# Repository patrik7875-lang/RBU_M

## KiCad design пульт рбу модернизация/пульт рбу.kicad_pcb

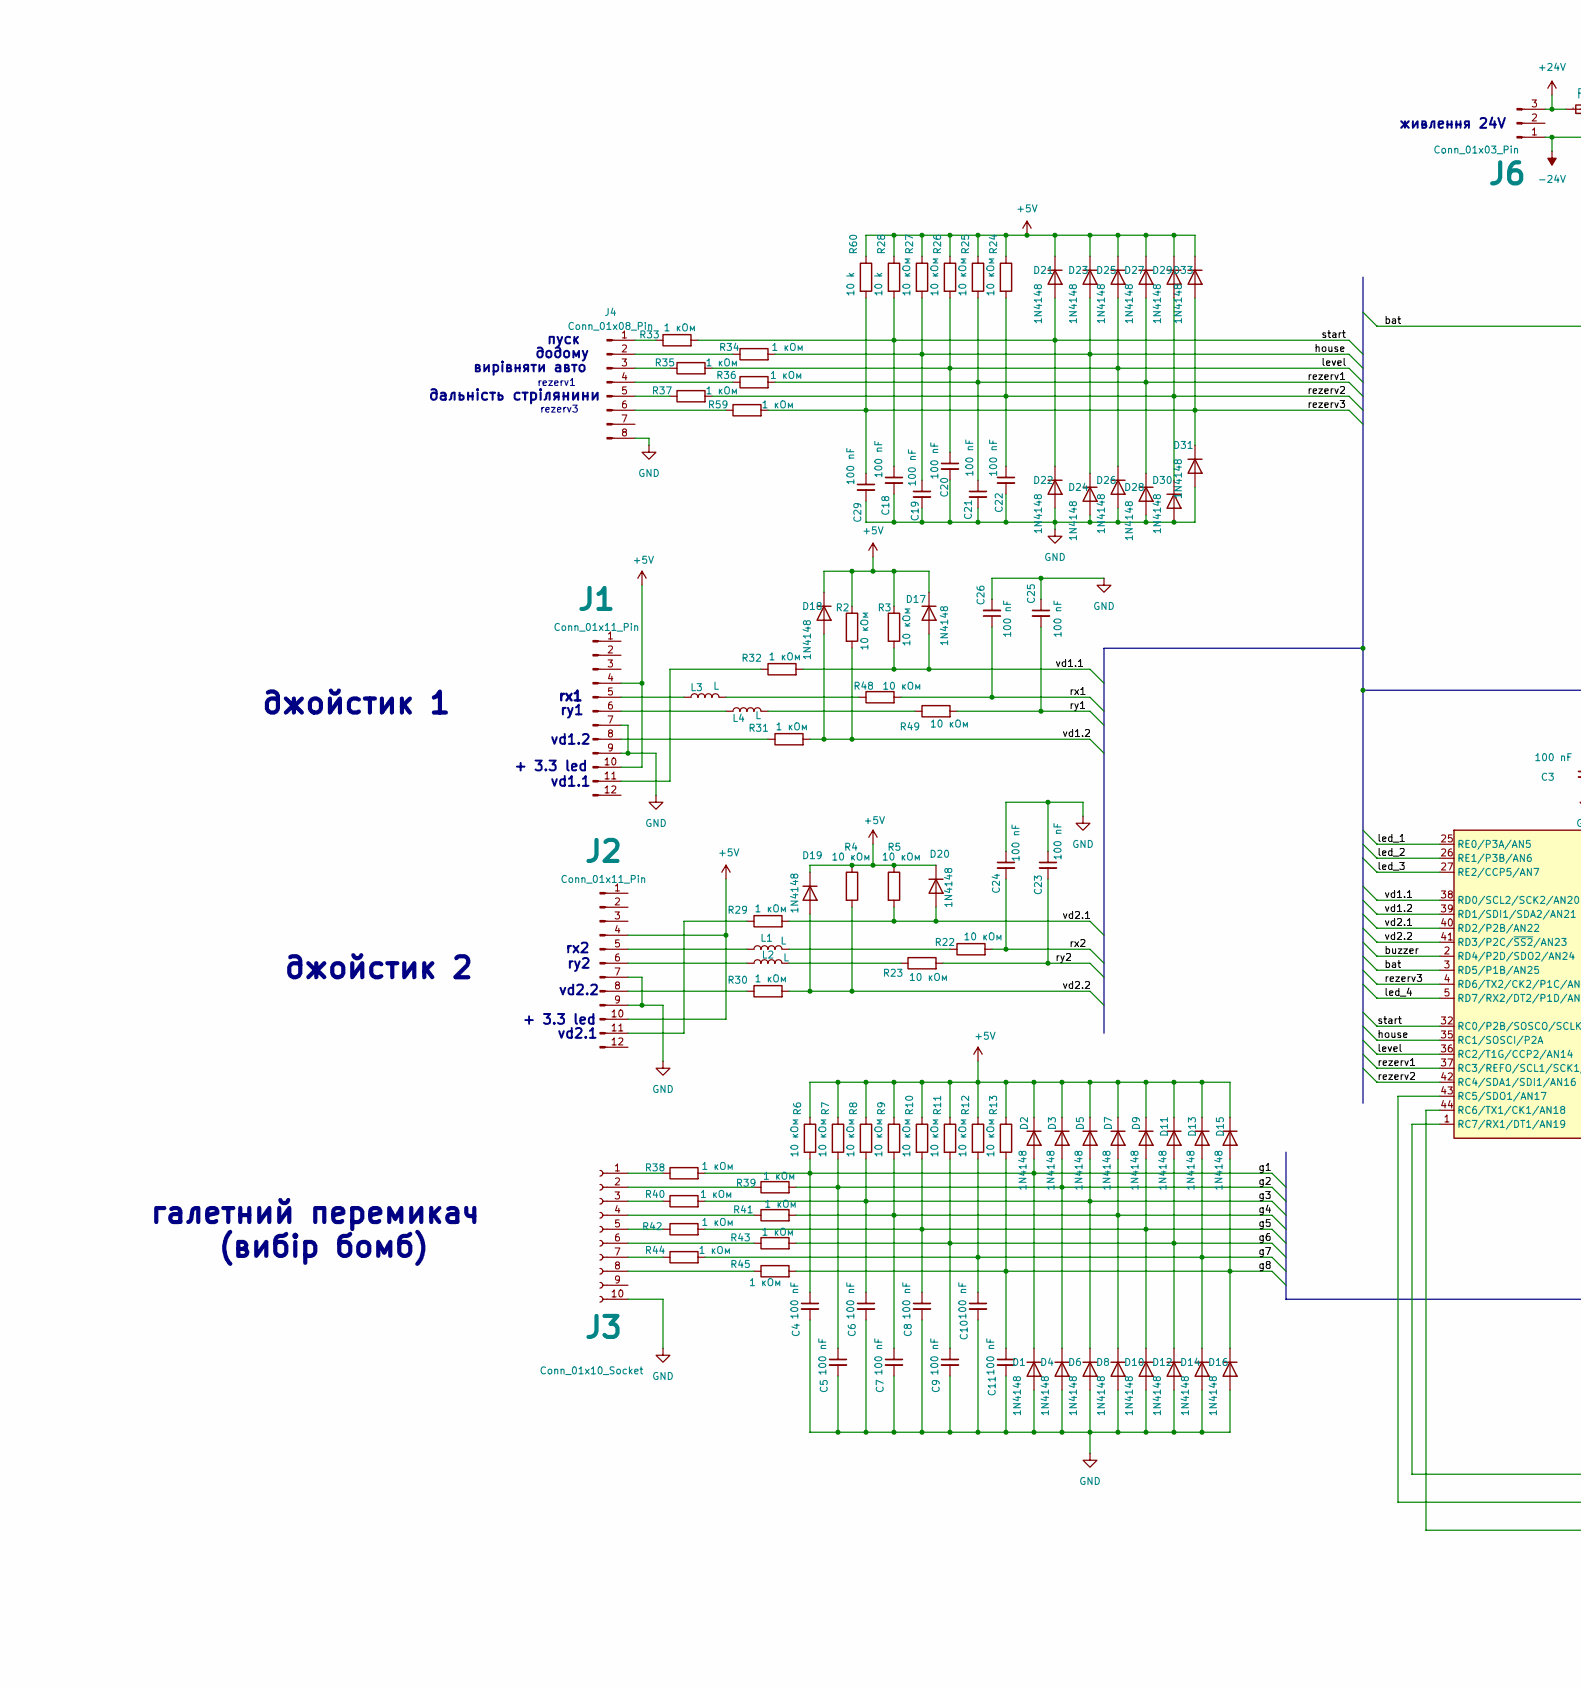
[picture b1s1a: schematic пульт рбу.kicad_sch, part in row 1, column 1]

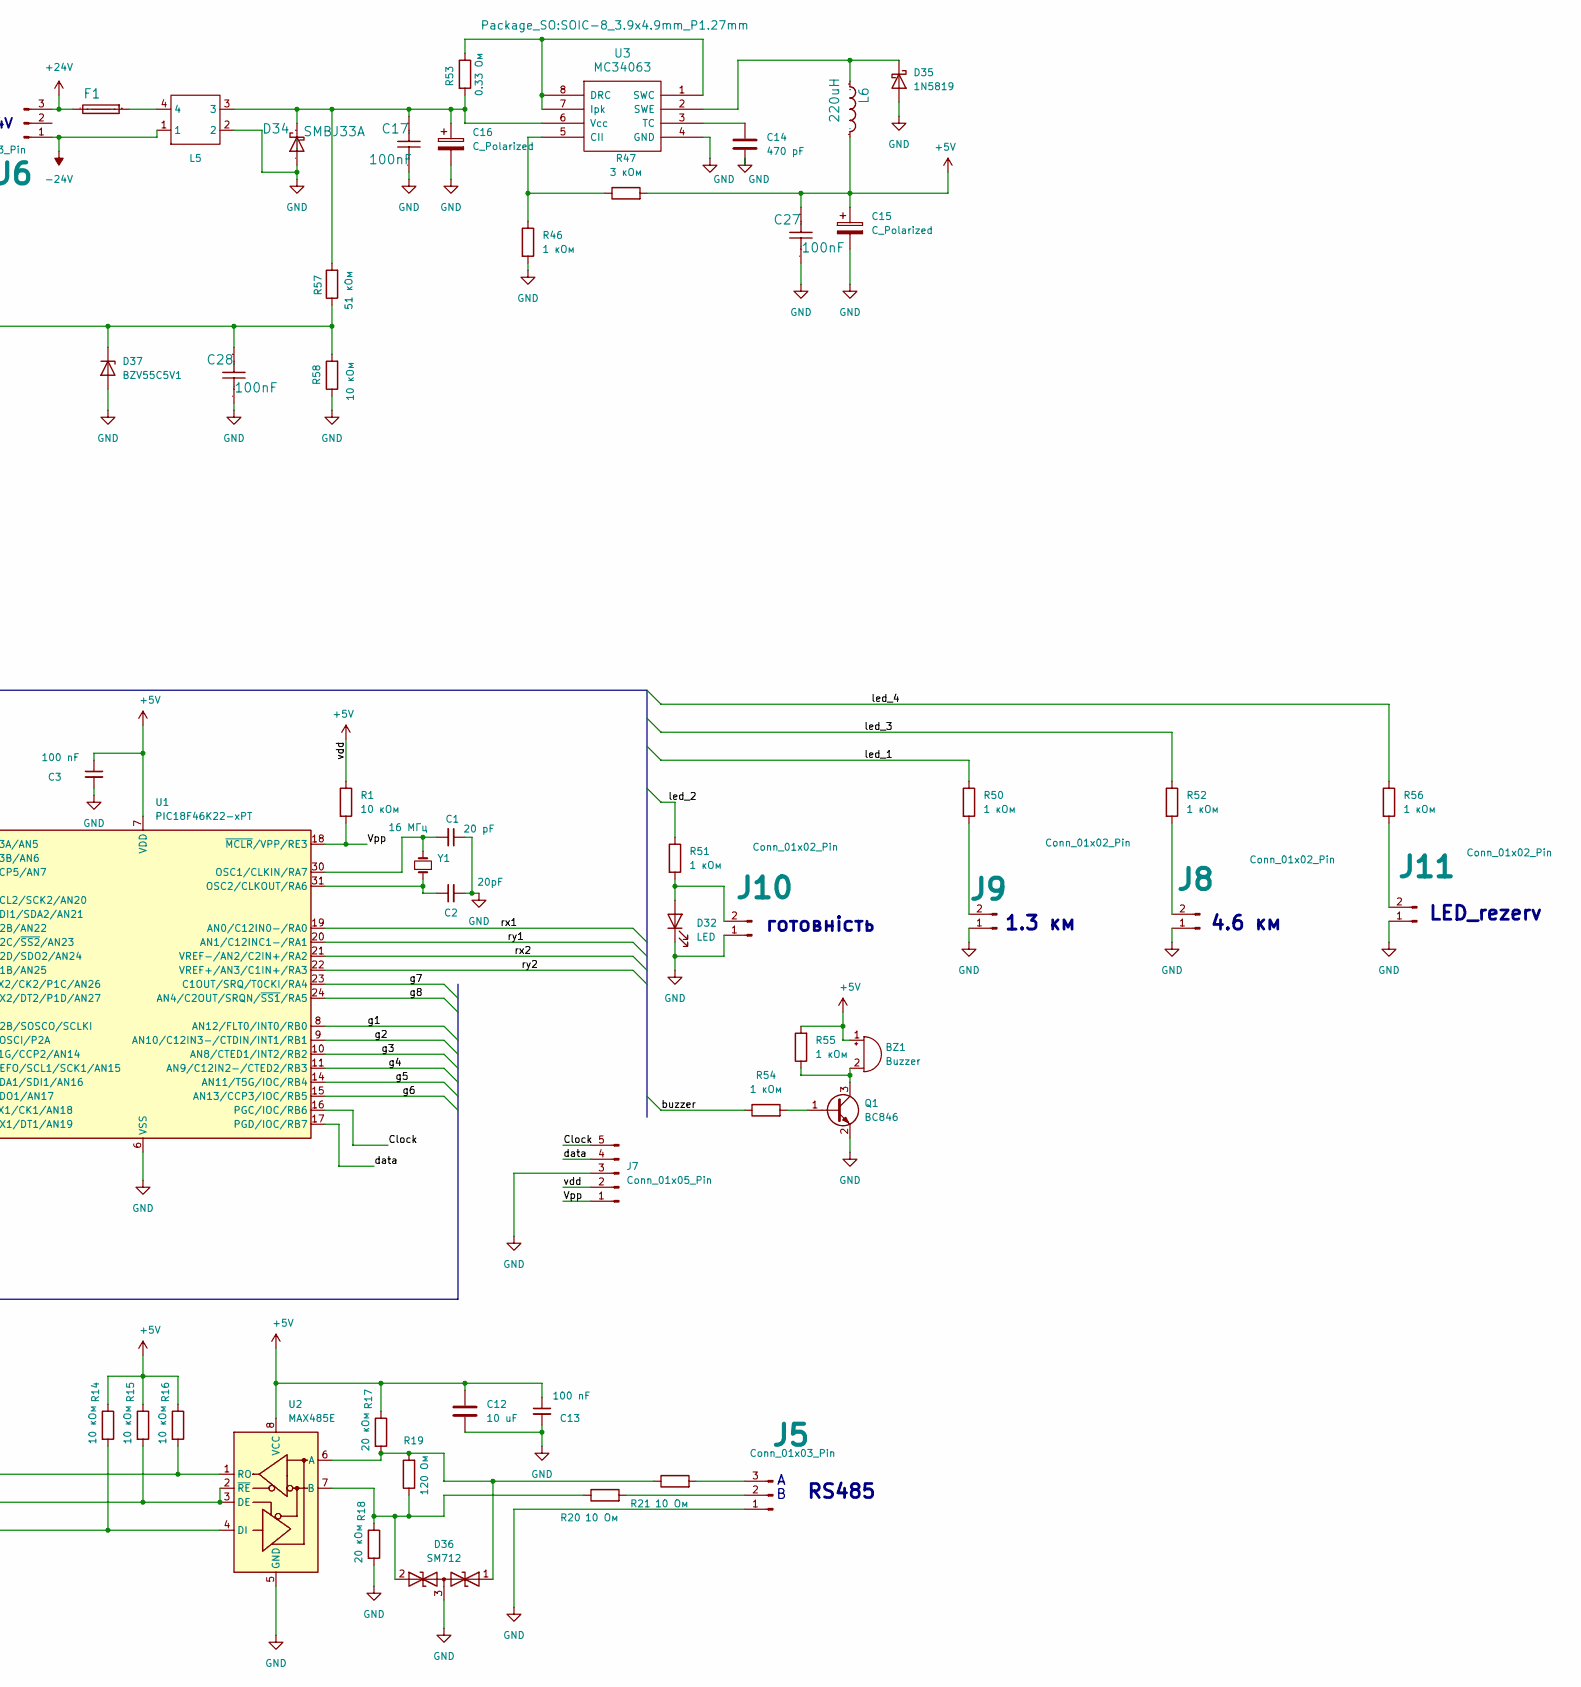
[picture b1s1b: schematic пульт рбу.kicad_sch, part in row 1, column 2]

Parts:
BZ1: Buzzer; Buzzer_12x9.5RM7.6
C1: 20 pF; C_0805_2012Metric
C2: 20pF; C_0805_2012Metric
C3, C4, C5, C6, C7, C8, C9, C10, C11, C13, C18, C19, C20, C21, C22, C23, C24, C25, C26, C29: 100 nF; C_1206_3216Metric
C12: 10 uF; C_1206_3216Metric
C14: 470 pF; C_0805_2012Metric
C15, C16: C_Polarized; C_Radial_D10.0mm_H16.0mm_P5.00mm
C17, C27, C28: 100nF; C_1206_3216Metric; Manufacturer Part FCC0805B104M500DT
D1, D2, D3, D4, D5, D6, D7, D8, D9, D10, D11, D12, D13, D14, D15, D16, D17, D18, D19, D20, D21, D22, D23, D24, D25, D26, D27, D28, D29, D30, D31, D33: 1N4148; D_SOD-123
D32: LED; LED_1206_3216Metric
D34: SMBJ33A; D_SMB
D35: 1N5819; D_DO-41_SOD81_P10.16mm_Horizontal
D36: SM712; SOT-23
D37: BZV55C5V1; D_MiniMELF
F1: 0.5 A; Fuse_1206_3216Metric; Manufacturer Part JFC2410-0200FS
J1, J2: Conn_01x11_Pin; JST_PH_B12B-PH-K_1x12_P2.00mm_Vertical
J3: Conn_01x10_Socket; Molex_KK-254_AE-6410-10A_1x10_P2.54mm_Vertical
J4: Conn_01x08_Pin; Molex_KK-254_AE-6410-08A_1x08_P2.54mm_Vertical
J5, J6: Conn_01x03_Pin; Molex_KK-254_AE-6410-03A_1x03_P2.54mm_Vertical
J7: Conn_01x05_Pin; PinHeader_1x05_P2.54mm_Vertical
J8, J9, J10, J11: Conn_01x02_Pin; JST_PH_B2B-PH-K_1x02_P2.00mm_Vertical
L1, L2, L3, L4: L; L_0805_2012Metric
L5: SSRH7H-M20016
L6: 220uH; L_Changjiang_FXL0840; Manufacturer Part CYL104R-10UH
Q1: BC846; SOT-23
R1, R4, R5: 10 кОм; Fuse_1206_3216Metric
R2, R3, R6, R7, R8, R9, R10, R11, R12, R13, R14, R15, R16, R24, R25, R26, R27: 10 кОм; R_1206_3216Metric
R17, R18: 20 кОм; R_1206_3216Metric
R19: 120 Ом; R_1206_3216Metric
R20, R21: 10 Ом; R_1206_3216Metric
R22, R23, R48, R49, R58: 10 кОм; R_0805_2012Metric
R28, R60: 10 k; R_1206_3216Metric
R29, R30, R31, R32, R33, R34, R35, R36, R37, R38, R39, R40, R41, R42, R43, R44, R45, R46, R50, R51, R52, R54, R55, R56, R59: 1 кОм; R_0805_2012Metric
R47: 3 кОм; R_0805_2012Metric
R53: 0.33 Ом; R_Axial_DIN0207_L6.3mm_D2.5mm_P2.54mm_Vertical
R57: 51 кОм; R_0805_2012Metric
U1: PIC18F46K22-xPT; TQFP-44_10x10mm_P0.8mm
U2: MAX485E; SOIC-8_3.9x4.9mm_P1.27mm
U3: MC34063; SOIC-8_3.9x4.9mm_P1.27mm
Y1: 16 МГц; Crystal_HC18-U_Vertical

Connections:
+5V: BZ1.1 (+), C3.1, C12.1, C13.1, C15.1, C27.1, D2.1 (K), D3.1 (K), D5.1 (K), D7.1 (K), D9.1 (K), D11.1 (K), D13.1 (K), D15.1 (K), D17.1 (K), D18.1 (K), D19.1 (K), D20.1 (K), D21.1 (K), D23.1 (K), D25.1 (K), D27.1 (K), D29.1 (K), D33.1 (K), J1.4, J1.10, J2.4, J2.10, J7.2, L6.2, R1.1, R2.1, R3.1, R4.1, R5.1, R6.1, R7.1, R8.1, R9.1, R10.1, R11.1, R12.1, R13.1, R14.1, R15.1, R16.1, R17.1, R24.1, R25.1, R26.1, R27.1, R28.1, R47.2, R55.2, R60.1, U1.7 (VDD), U1.28 (VDD), U2.8 (VCC)
+24V: F1.2, J6.3
-24V: J6.1, L5.1
/Clock: J7.5, U1.16 (PGC/IOC/RB6)
/Vpp: J7.1, R1.2, U1.18 (~MCLR/VPP/RE3)
/bat: C28.1, D37.1 (K), R57.1, R58.2, U1.3 (RD5/P1B/AN25)
/buzzer: R54.1, U1.2 (RD4/P2D/SDO2/AN24)
/data: J7.4, U1.17 (PGD/IOC/RB7)
/g1: C4.1, D1.1 (K), D2.2 (A), R6.2, R38.2, U1.8 (AN12/FLT0/INT0/RB0)
/g2: C5.1, D3.2 (A), D4.1 (K), R7.2, R39.2, U1.9 (AN10/C12IN3-/CTDIN/INT1/RB1)
/g3: C6.1, D5.2 (A), D6.1 (K), R8.2, R40.2, U1.10 (AN8/CTED1/INT2/RB2)
/g4: C7.1, D7.2 (A), D8.1 (K), R9.2, R41.2, U1.11 (AN9/C12IN2-/CTED2/RB3)
/g5: C8.1, D9.2 (A), D10.1 (K), R10.2, R42.2, U1.14 (AN11/T5G/IOC/RB4)
/g6: C9.1, D11.2 (A), D12.1 (K), R11.2, R43.2, U1.15 (AN13/CCP3/IOC/RB5)
/g7: C10.1, D13.2 (A), D14.1 (K), R12.2, R44.2, U1.23 (C1OUT/SRQ/T0CKI/RA4)
/g8: C11.1, D15.2 (A), D16.1 (K), R13.2, R45.2, U1.24 (AN4/C2OUT/SRQN/~SS1/RA5)
/house: C19.1, D23.2 (A), D24.1 (K), R27.2, R34.2, U1.35 (RC1/SOSCI/P2A)
/led_1: R50.1, U1.25 (RE0/P3A/AN5)
/led_2: R51.1, U1.26 (RE1/P3B/AN6)
/led_3: R52.1, U1.27 (RE2/CCP5/AN7)
/led_4: R56.1, U1.5 (RD7/RX2/DT2/P1D/AN27)
/level: C20.1, D25.2 (A), D26.1 (K), R26.2, R35.2, U1.36 (RC2/T1G/CCP2/AN14)
/rezerv1: C21.1, D27.2 (A), D28.1 (K), R25.2, R36.2, U1.37 (RC3/REFO/SCL1/SCK1/AN15)
/rezerv2: C22.1, D29.2 (A), D30.1 (K), R24.2, R37.2, U1.42 (RC4/SDA1/SDI1/AN16)
/rezerv3: C29.1, D31.1 (K), D33.2 (A), R59.2, R60.2, U1.4 (RD6/TX2/CK2/P1C/AN26)
/rx1: C26.1, R48.2, U1.19 (AN0/C12IN0-/RA0)
/rx2: C24.2, R22.2, U1.21 (VREF-/AN2/C2IN+/RA2)
/ry1: C25.2, R49.2, U1.20 (AN1/C12INC1-/RA1)
/ry2: C23.2, R23.2, U1.22 (VREF+/AN3/C1IN+/RA3)
/start: C18.1, D21.2 (A), D22.1 (K), R28.2, R33.2, U1.32 (RC0/P2B/SOSCO/SCLKI)
/vd1.1: D17.2 (A), R3.2, R32.2, U1.38 (RD0/SCL2/SCK2/AN20)
/vd1.2: D18.2 (A), R2.2, R31.2, U1.39 (RD1/SDI1/SDA2/AN21)
/vd2.1: D20.2 (A), R5.2, R29.2, U1.40 (RD2/P2B/AN22)
/vd2.2: D19.2 (A), R4.2, R30.2, U1.41 (RD3/P2C/~SS2/AN23)
GND: C1.1, C2.2, C3.2, C4.2, C5.2, C6.2, C7.2, C8.2, C9.2, C10.2, C11.2, C12.2, C13.2, C14.2, C15.2, C16.2, C17.2, C18.2, C19.2, C20.2, C21.2, C22.2, C23.1, C24.1, C25.1, C26.2, C27.2, C28.2, C29.2, D1.2 (A), D4.2 (A), D6.2 (A), D8.2 (A), D10.2 (A), D12.2 (A), D14.2 (A), D16.2 (A), D22.2 (A), D24.2 (A), D26.2 (A), D28.2 (A), D30.2 (A), D31.2 (A), D32.1 (K), D34.2 (A), D35.2 (A), D36.3 (common), D37.2 (A), J1.7, J1.9, J2.7, J2.9, J3.10, J4.8, J5.1, J7.3, J8.1, J9.1, J10.1, J11.1, L5.2, Q1.2 (E), R18.2, R46.2, R58.1, U1.6 (VSS), U1.29 (VSS), U2.5 (GND), U3.4 (GND)
unnamed: BZ1.2 (-), Q1.3 (C), R55.1
unnamed: D32.2 (A), J10.2, R51.2
unnamed: C16.1, C17.1, D34.1 (K), L5.3, R53.2, R57.2, U3.6 (Vcc)
unnamed: D35.1 (K), L6.1, U3.2 (SWE)
unnamed: D36.1 (A1), R17.2, R19.2, R21.1, U2.6 (A)
unnamed: D36.2 (A2), R18.1, R19.1, R20.1, U2.7 (B)
unnamed: F1.1, L5.4
unnamed: J1.5, L3.1
unnamed: J1.6, L4.1
unnamed: J1.8, R31.1
unnamed: J1.11, R32.1
unnamed: J2.5, L1.1
unnamed: J2.6, L2.1
unnamed: J2.8, R30.1
unnamed: J2.11, R29.1
unnamed: J3.1, R38.1
unnamed: J3.2, R39.1
unnamed: J3.3, R40.1
unnamed: J3.4, R41.1
unnamed: J3.5, R42.1
unnamed: J3.6, R43.1
unnamed: J3.7, R44.1
unnamed: J3.8, R45.1
unnamed: J4.1, R33.1
unnamed: J4.2, R34.1
unnamed: J4.3, R35.1
unnamed: J4.4, R36.1
unnamed: J4.5, R37.1
unnamed: J4.6, R59.1
unnamed: J5.2, R20.2
unnamed: J5.3, R21.2
unnamed: J8.2, R52.2
unnamed: J9.2, R50.2
unnamed: J11.2, R56.2
unnamed: L1.2, R22.1
unnamed: L2.2, R23.1
unnamed: L3.2, R48.1
unnamed: L4.2, R49.1
unnamed: Q1.1 (B), R54.2
unnamed: C1.2, U1.30 (OSC1/CLKIN/RA7), Y1.2
unnamed: C2.1, U1.31 (OSC2/CLKOUT/RA6), Y1.1
unnamed: R15.2, U1.43 (RC5/SDO1/AN17), U2.2 (~RE), U2.3 (DE)
unnamed: R14.2, U1.44 (RC6/TX1/CK1/AN18), U2.4 (DI)
unnamed: R16.2, U1.1 (RC7/RX1/DT1/AN19), U2.1 (RO)
unnamed: R46.1, R47.1, U3.5 (CII)
unnamed: R53.1, U3.1 (SWC), U3.7 (Ipk), U3.8 (DRC)
unnamed: C14.1, U3.3 (TC)

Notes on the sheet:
vd1.2
RS485
вирівняти авто
+ 3.3 led
джойстик 1
додому
ry1
vd2.2
vd1.1
rx1
rezerv3
галетний перемикач (вибір бомб)
джойстик 2
дальність стрілянини
vd2.1
1.3 км
rx2
живлення 24V
4.6 км
ry2
пуск
LED_rezerv
rezerv1
готовнiсть

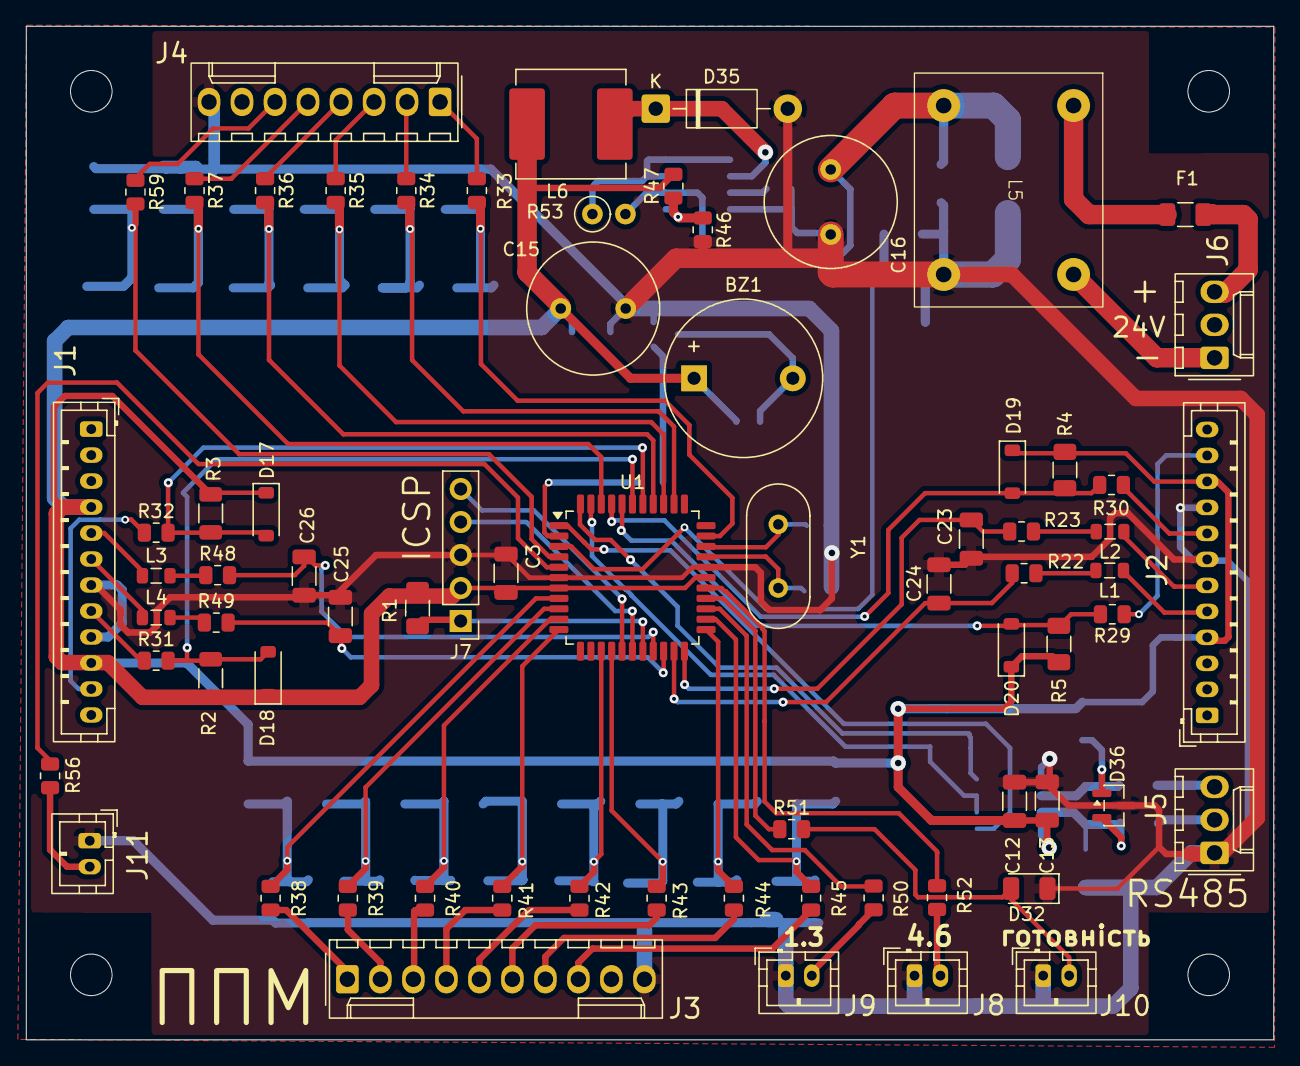
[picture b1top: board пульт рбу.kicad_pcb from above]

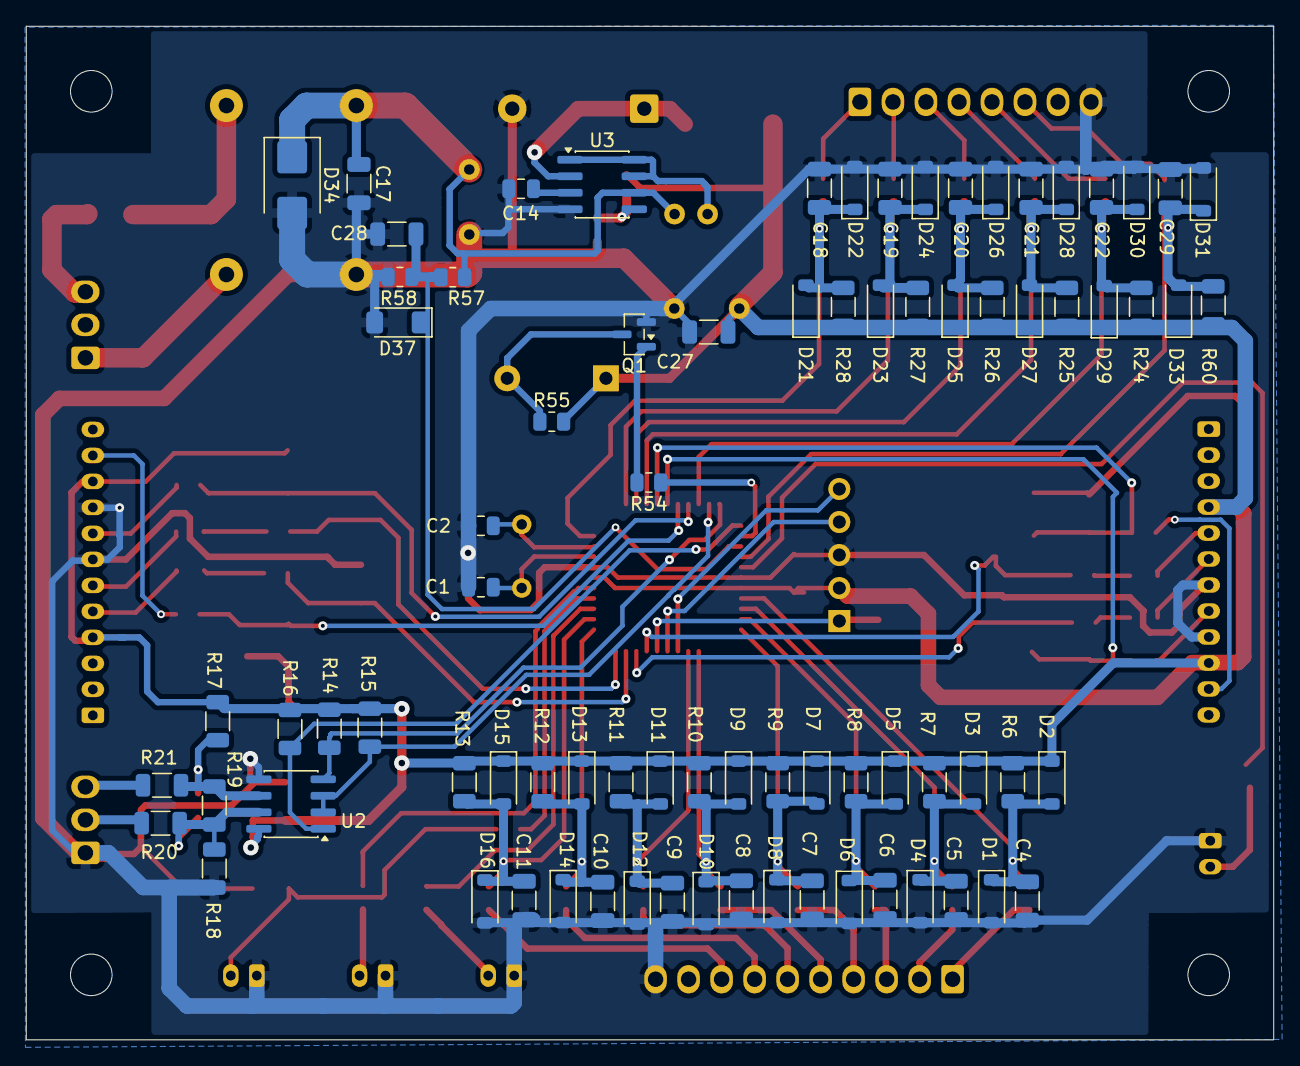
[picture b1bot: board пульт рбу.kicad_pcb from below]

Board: 2 copper layers, 96.0 x 78.0 mm, 150 parts (79 on the bottom side), 82 nets.

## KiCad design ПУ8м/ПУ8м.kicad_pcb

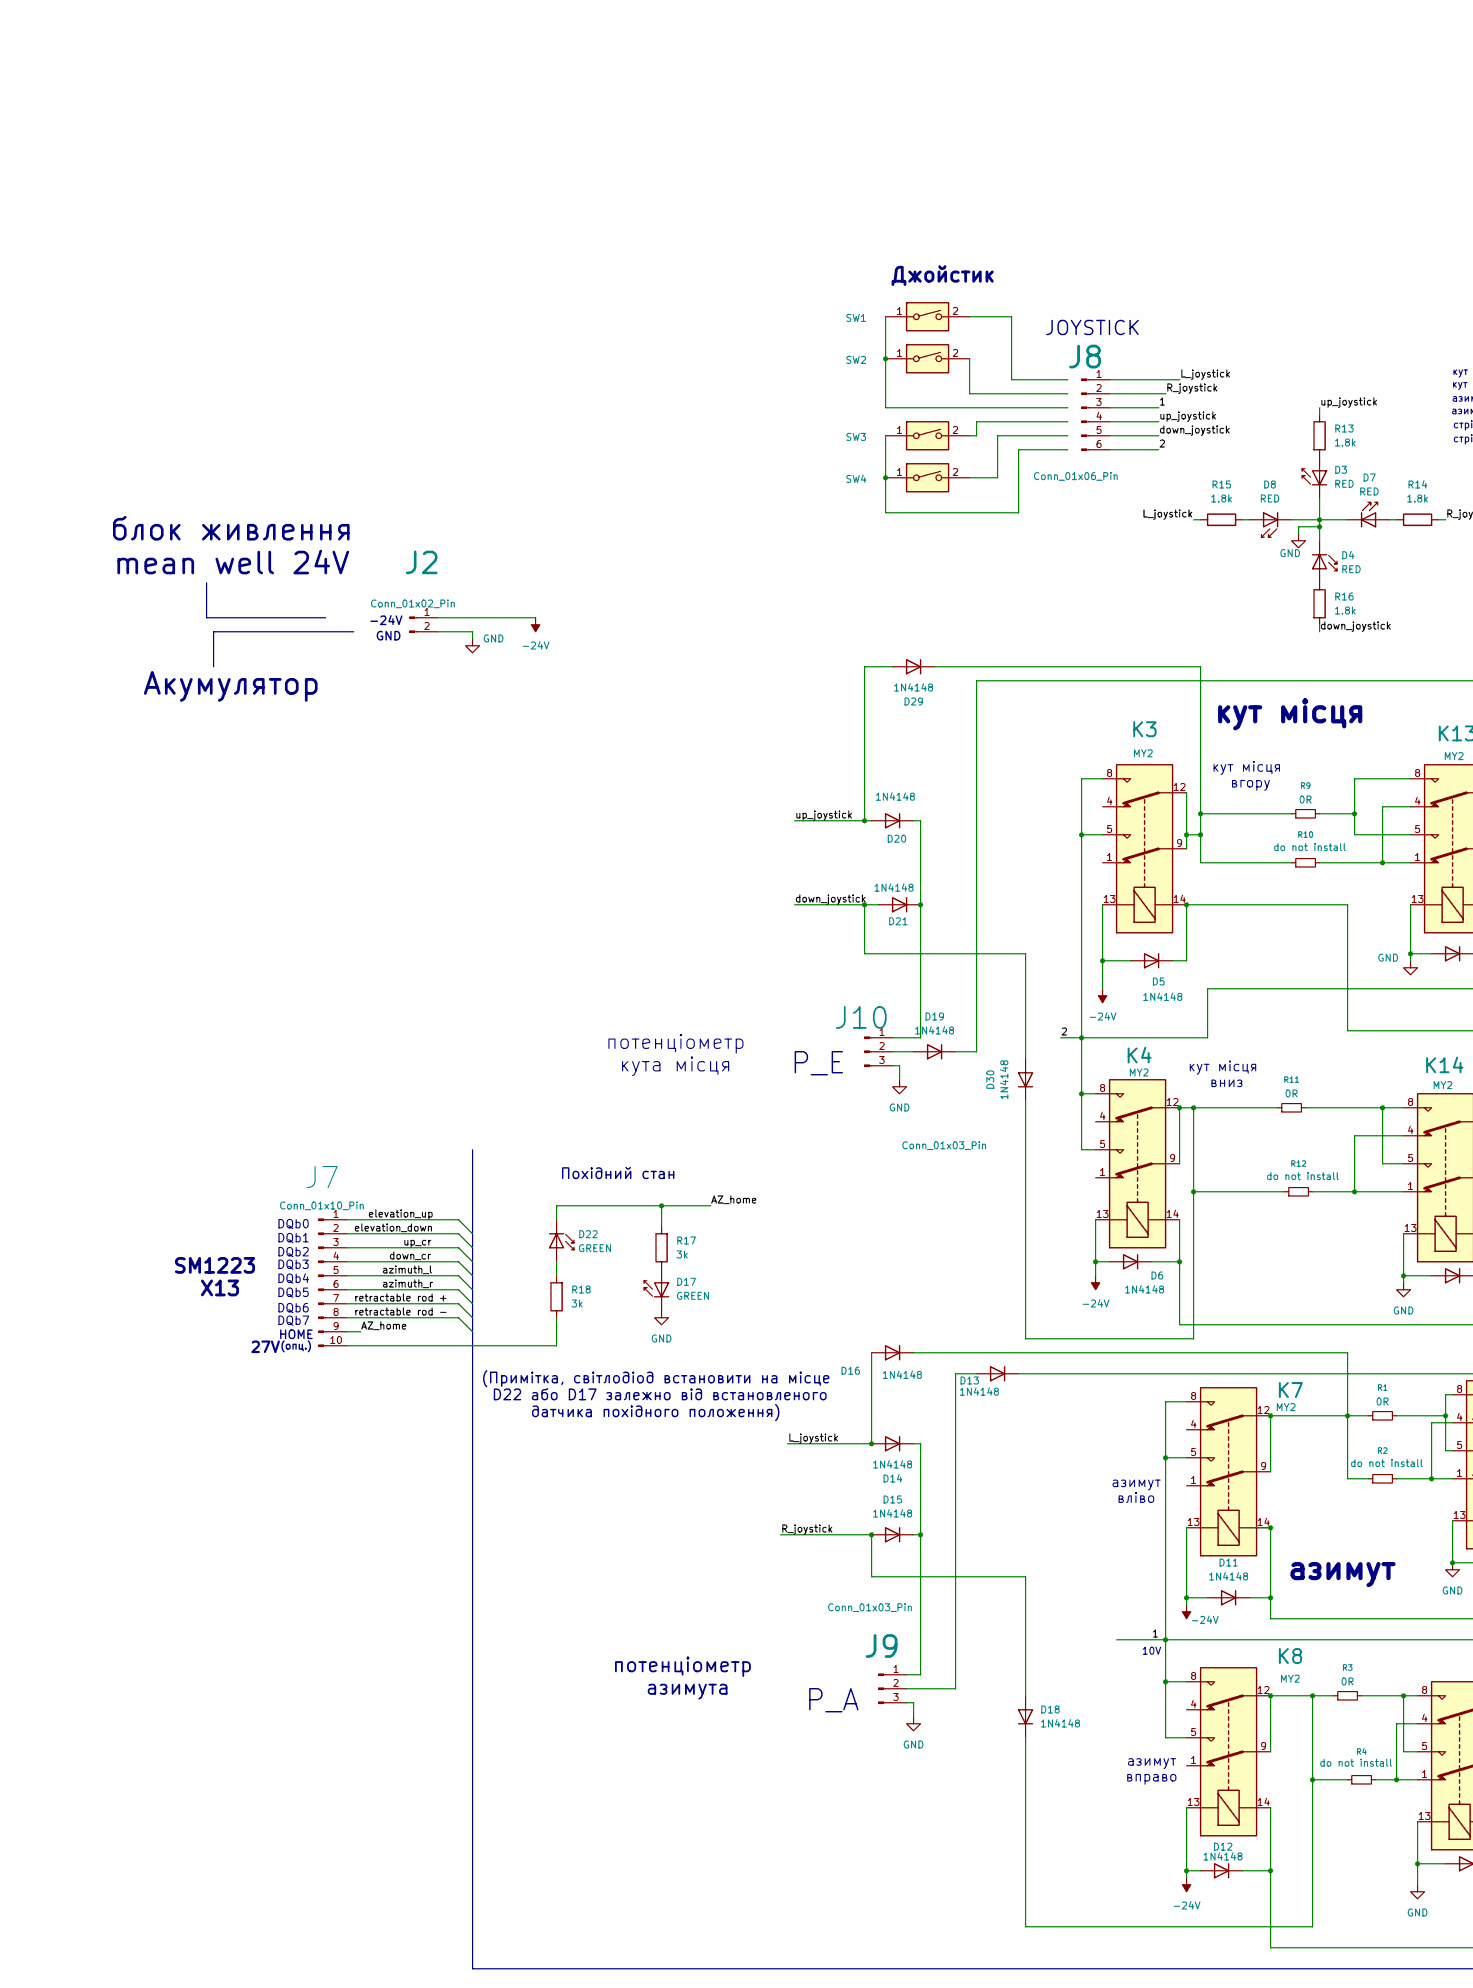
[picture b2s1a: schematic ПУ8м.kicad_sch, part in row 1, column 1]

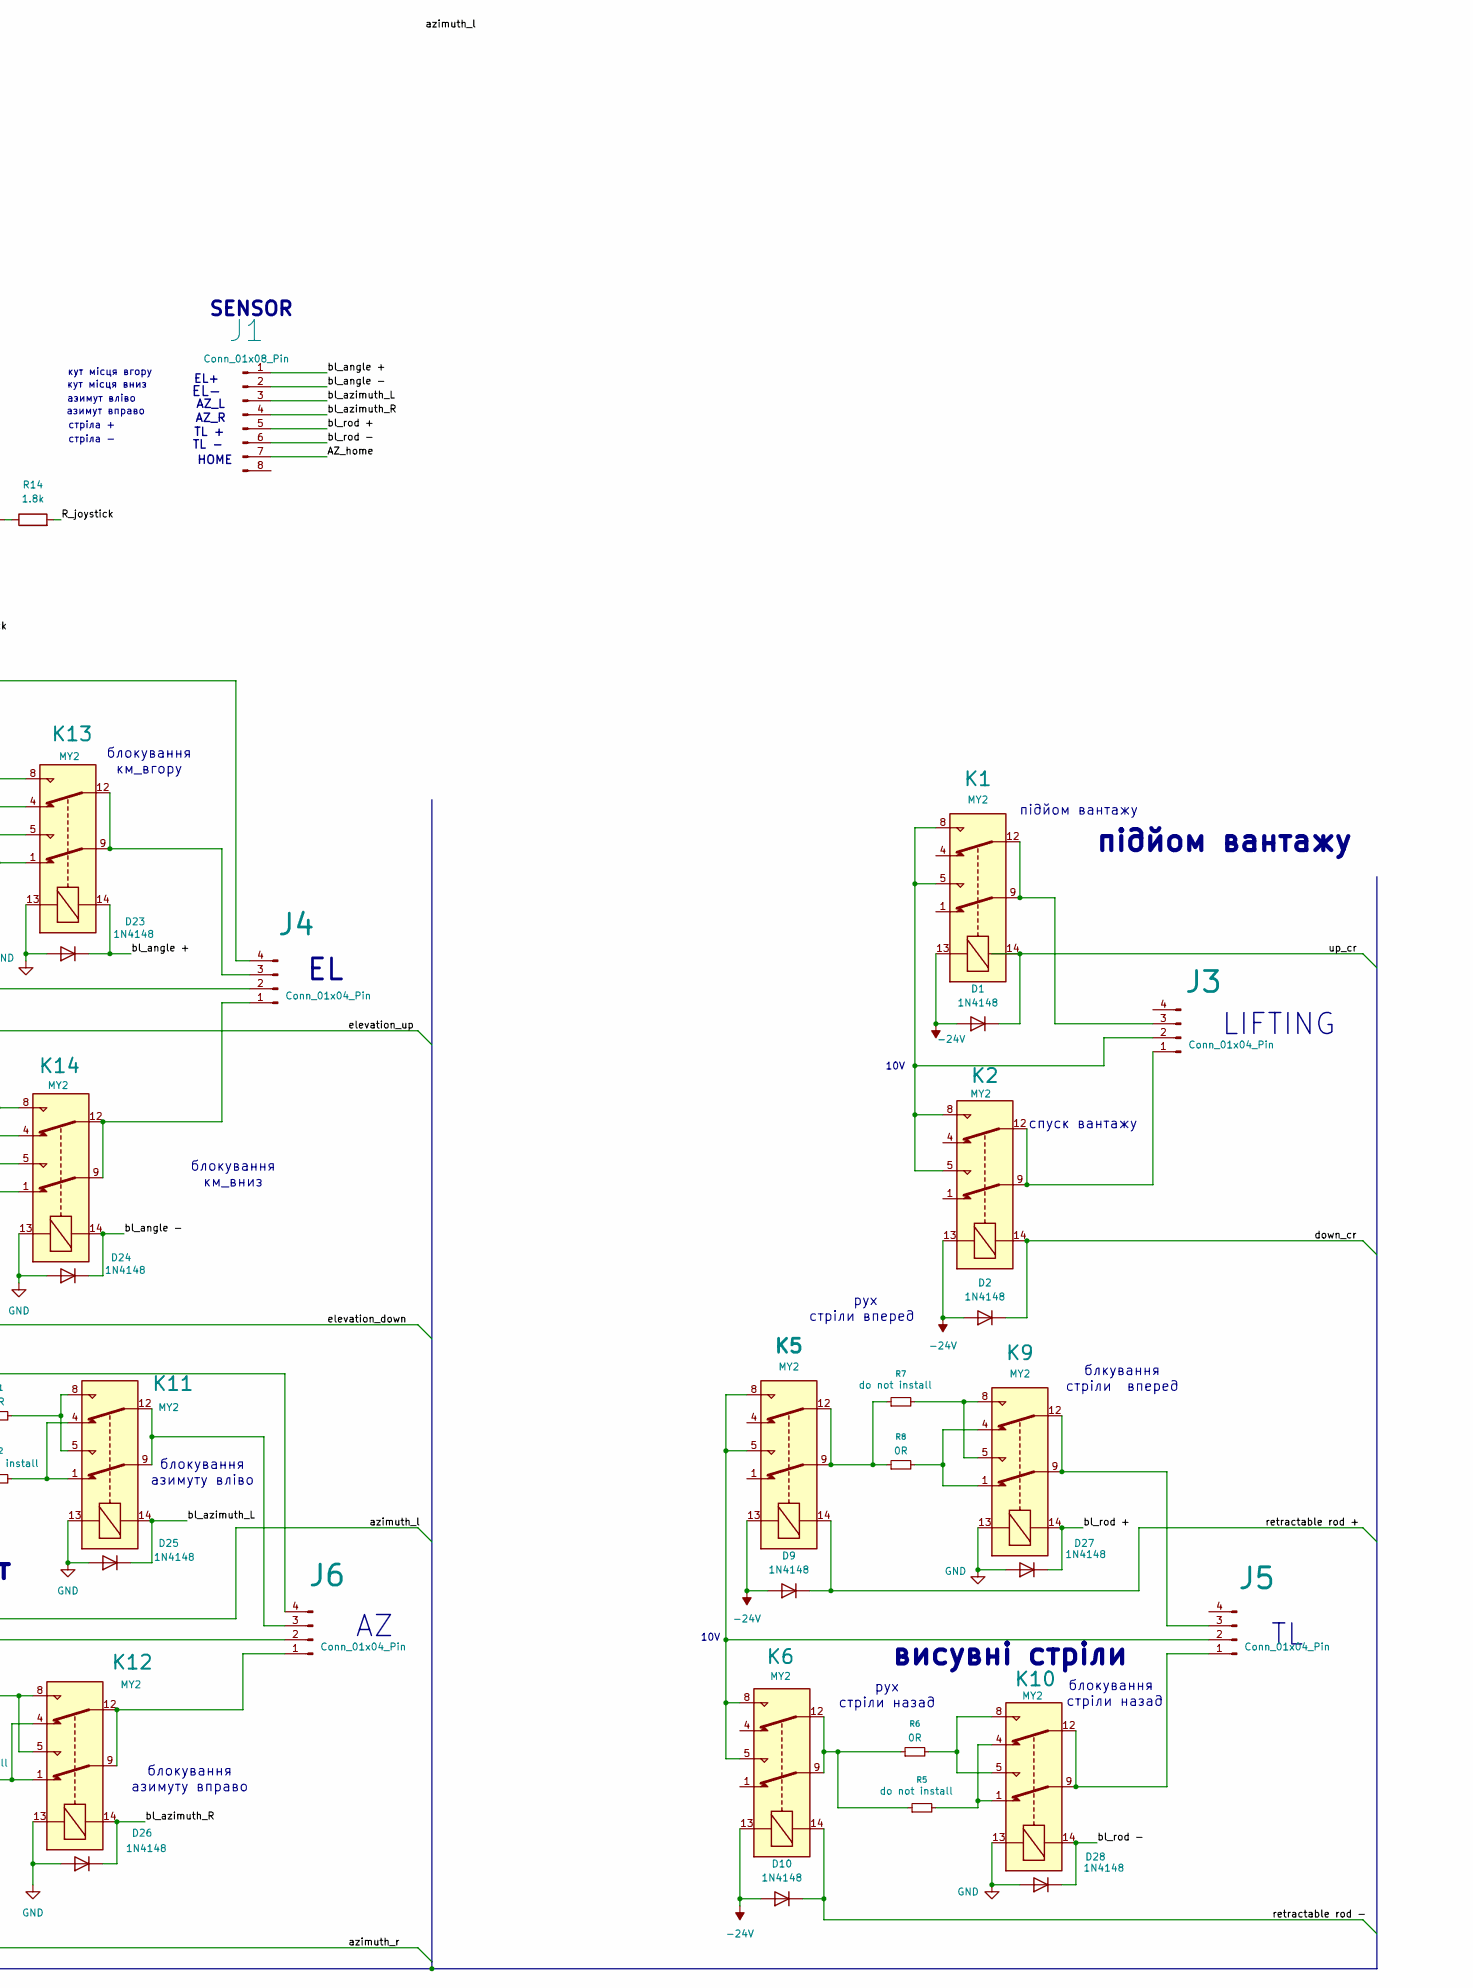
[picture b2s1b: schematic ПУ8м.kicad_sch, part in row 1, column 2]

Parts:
D1, D2, D5, D6, D9, D10, D11, D12, D13, D14, D15, D16, D18, D19, D20, D21, D23, D24, D25, D26, D27, D28, D29, D30: 1N4148; D_SOD-123
D3, D4, D7, D8: RED; LED_1206_3216Metric
D17, D22: GREEN; LED_1206_3216Metric
J1: Conn_01x08_Pin; TerminalBlock_Phoenix_PT-1,5-8-5.0-H_1x08_P5.00mm_Horizontal
J2: Conn_01x02_Pin; TerminalBlock_Phoenix_PT-1,5-2-5.0-H_1x02_P5.00mm_Horizontal
J3, J4, J5, J6: Conn_01x04_Pin; Molex_KK-254_AE-6410-04A_1x04_P2.54mm_Vertical
J7: Conn_01x10_Pin; TerminalBlock_Phoenix_MKDS-1,5-10_1x10_P5.00mm_Horizontal
J8: Conn_01x06_Pin; Molex_KK-254_AE-6410-06A_1x06_P2.54mm_Vertical
J9, J10: Conn_01x03_Pin; Molex_KK-254_AE-6410-03A_1x03_P2.54mm_Vertical
K1, K2, K3, K4, K5, K6, K7, K8, K9, K10, K11, K12, K13, K14: MY2
R1, R3, R6, R8, R9, R11: 0R; R_1206_3216Metric
R2, R4, R5, R7, R10, R12: do not install; R_1206_3216Metric
R13, R14, R15, R16: 1.8k; R_1206_3216Metric
R17, R18: 3k; R_1206_3216Metric
SW1, SW2, SW3, SW4: SW_DIP_x01

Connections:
-24V: D1.2 (A), D2.2 (A), D5.2 (A), D6.2 (A), D9.2 (A), D10.2 (A), D11.2 (A), D12.2 (A), J2.1, K1.13, K2.13, K3.13, K4.13, K5.13, K6.13, K7.13, K8.13
/1: J6.2, J8.3, K7.5, K7.8, K8.5, K8.8
/2: J4.2, J8.6, K3.5, K3.8, K4.5, K4.8
/AZ_home: D22.1 (K), J1.7, J7.9, R17.2
/L_joystick: D14.2 (A), D16.2 (A), J8.1, R15.1
/R_joystick: D15.2 (A), D18.2 (A), J8.2, R14.2
/azimuth_l: D11.1 (K), J7.5, K7.14
/azimuth_r: D12.1 (K), J7.6, K8.14
/bl_angle +: D23.1 (K), J1.1, K13.14
/bl_angle -: D24.1 (K), J1.2, K14.14
/bl_azimuth_L: D25.1 (K), J1.3, K11.14
/bl_azimuth_R: D26.1 (K), J1.4, K12.14
/bl_rod +: D27.1 (K), J1.5, K9.14
/bl_rod -: D28.1 (K), J1.6, K10.14
/down_cr: D2.1 (K), J7.4, K2.14
/down_joystick: D21.2 (A), D30.2 (A), J8.5, R16.2
/elevation_down: D6.1 (K), J7.2, K4.14
/elevation_up: D5.1 (K), J7.1, K3.14
/retractable rod +: D9.1 (K), J7.7, K5.14
/retractable rod -: D10.1 (K), J7.8, K6.14
/up_cr: D1.1 (K), J7.3, K1.14
/up_joystick: D20.2 (A), D29.2 (A), J8.4, R13.1
GND: D3.1 (K), D4.1 (K), D7.1 (K), D8.1 (K), D17.1 (K), D23.2 (A), D24.2 (A), D25.2 (A), D26.2 (A), D27.2 (A), D28.2 (A), J2.2, J9.3, J10.3, K9.13, K10.13, K11.13, K12.13, K13.13, K14.13
unnamed: D3.2 (A), R13.2
unnamed: D4.2 (A), R16.1
unnamed: D7.2 (A), R14.1
unnamed: D8.2 (A), R15.2
unnamed: D13.2 (A), J9.2
unnamed: D13.1 (K), J6.4
unnamed: D14.1 (K), D15.1 (K), J9.1
unnamed: D16.1 (K), K7.9, K7.12, R1.1, R2.1
unnamed: D17.2 (A), R17.1
unnamed: D18.1 (K), K8.9, K8.12, R3.1, R4.1
unnamed: D19.2 (A), J10.2
unnamed: D19.1 (K), J4.4
unnamed: D20.1 (K), D21.1 (K), J10.1
unnamed: D22.2 (A), R18.2
unnamed: D29.1 (K), K3.9, K3.12, R9.1, R10.1
unnamed: D30.1 (K), K4.9, K4.12, R11.1, R12.1
unnamed: J3.1, K2.9, K2.12
unnamed: J3.2, K1.5, K1.8, K2.5, K2.8
unnamed: J3.3, K1.9, K1.12
unnamed: J4.1, K14.9, K14.12
unnamed: J4.3, K13.9, K13.12
unnamed: J5.1, K10.9, K10.12
unnamed: J5.2, K5.5, K5.8, K6.5, K6.8
unnamed: J5.3, K9.9, K9.12
unnamed: J6.1, K12.9, K12.12
unnamed: J6.3, K11.9, K11.12
unnamed: J7.10, R18.1
unnamed: K5.9, K5.12, R7.1, R8.1
unnamed: K6.9, K6.12, R5.1, R6.1
unnamed: K9.1, K9.4, R8.2
unnamed: K9.5, K9.8, R7.2
unnamed: K10.1, K10.4, R5.2
unnamed: K10.5, K10.8, R6.2
unnamed: K11.1, K11.4, R2.2
unnamed: K11.5, K11.8, R1.2
unnamed: K12.1, K12.4, R4.2
unnamed: K12.5, K12.8, R3.2
unnamed: K13.1, K13.4, R10.2
unnamed: K13.5, K13.8, R9.2
unnamed: K14.1, K14.4, R12.2
unnamed: K14.5, K14.8, R11.2
unnamed: SW1.1, SW2.1
unnamed: SW3.1, SW4.1

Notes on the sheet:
10V
AZ_L
азимут вправо
стріла -
TL -
кут місця вниз
EL+
висувні стріли
SM1223 X13
(Примітка, світлодіод встановити на місце D22 або D17 залежно від встановленого датчика похідного положення)
потенціометр азимута
блокування азимуту вліво
AZ_R
EL-
рух стріли назад
блкування стріли вперед
блокування стріли назад
P_A
стріла +
DQb7
Похідний стан
блокування км_вниз
DQb2
DQb4
азимут
Джойстик
блокування км_вгору
блок живлення mean well 24V
-24V
DQb5
кут місця
рух стріли вперед
азимут вліво
підйом вантажу
JOYSTICK
DQb6
Акумулятор
кут місця вгору
27V
кут місця вгору

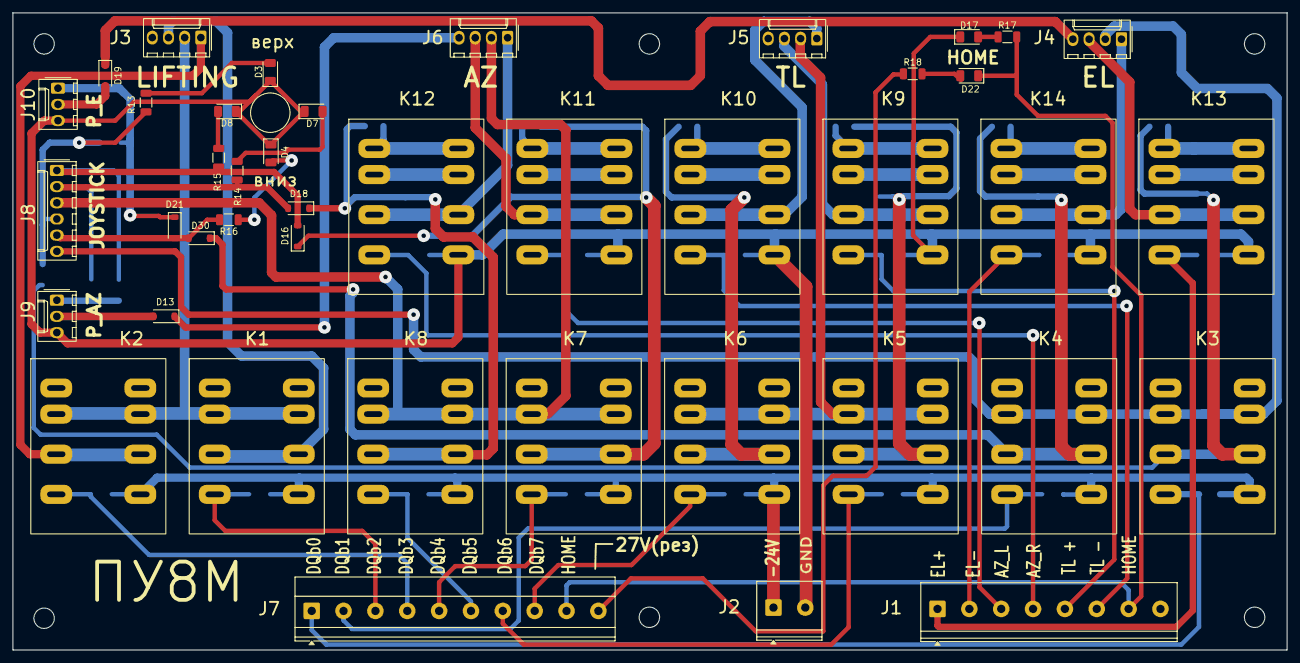
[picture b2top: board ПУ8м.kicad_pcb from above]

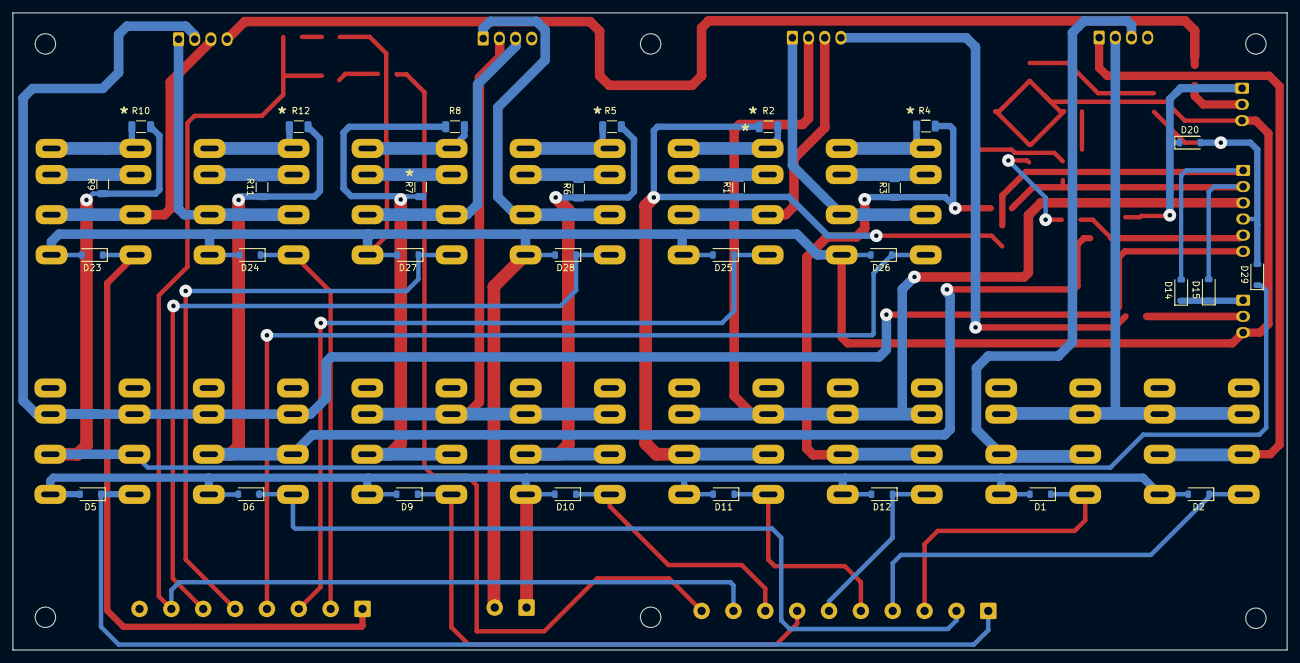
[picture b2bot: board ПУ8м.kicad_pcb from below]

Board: 2 copper layers, 200.0 x 100.0 mm, 72 parts (30 on the bottom side), 64 nets.
